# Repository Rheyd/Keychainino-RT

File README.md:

# Keychainino-RT
this is a fork of the original KeychaininoTHT https://github.com/alessandromatera/KeyChainino
this version allows you to make the Keychainino in a single layer PCB, with some wire bridges, but none the less allows you to make it, remember to support the original creator, Alessandromatera
Cheers.

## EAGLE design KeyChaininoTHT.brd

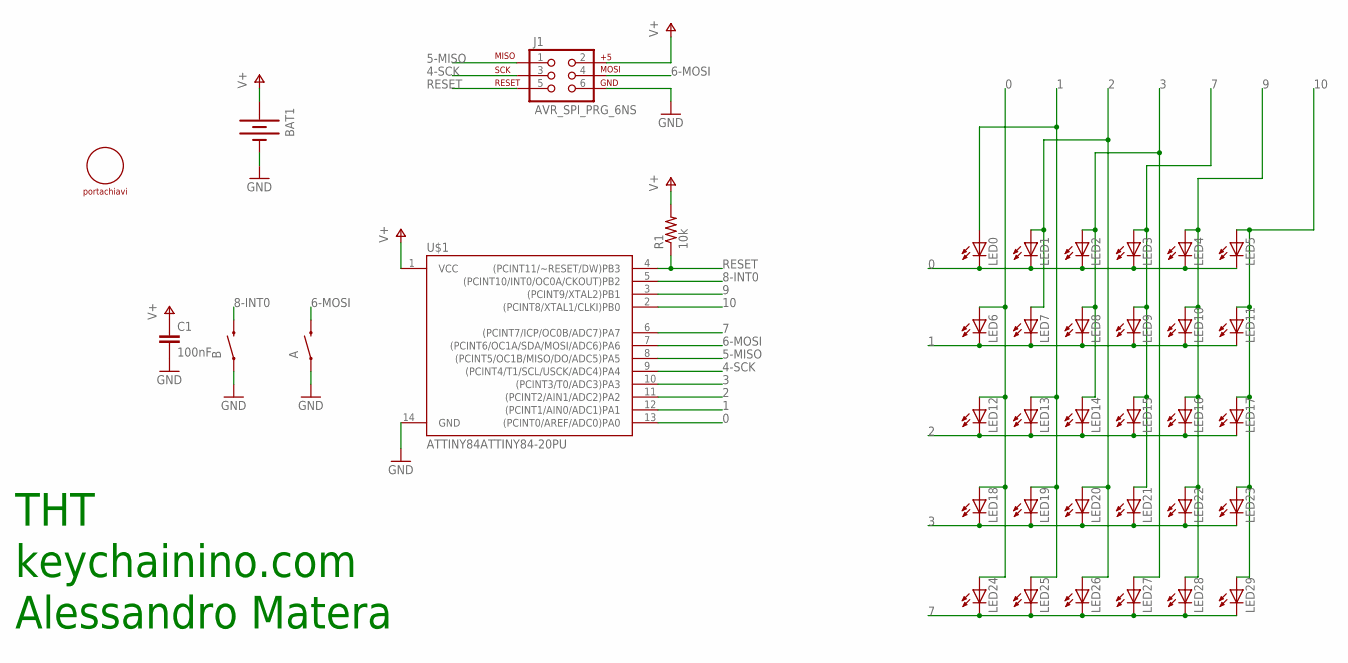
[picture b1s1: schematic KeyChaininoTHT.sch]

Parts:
A: SWITCH-MOMENTARY-2PTH; TACTILE-PTH
B: SWITCH-MOMENTARY-2PTH; TACTILE-PTH
BAT1: BATTERY20PTH; BATTCOM_20MM_PTH
C1: 100nF; CAP-PTH-5MM
J1: AVR_SPI_PRG_6NS; 2X3-NS
LED0, LED1, LED2, LED3, LED4, LED5, LED6, LED7, LED8, LED9, LED10, LED11, LED12, LED13, LED14, LED15, LED16, LED17, LED18, LED19, LED20, LED21, LED22, LED23, LED24, LED25, LED26, LED27, LED28, LED29: LED5MM-KIT
R1: 10k; R1206
U$1: ATTINY84ATTINY84-20PU; DIL14
U$2: ANELLO-PORTACHIAVI; HOLE-PORTACHIAVI

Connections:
0: LED0.K (C), LED1.K (C), LED2.K (C), LED3.K (C), LED4.K (C), LED5.K (C), LED6.A, LED12.A, LED18.A, LED24.A, U$1.13 ((PCINT0/AREF/ADC0)PA0)
1: LED0.A, LED6.K (C), LED7.K (C), LED8.K (C), LED9.K (C), LED10.K (C), LED11.K (C), LED13.A, LED19.A, LED25.A, U$1.12 ((PCINT1/AIN0/ADC1)PA1)
2: LED1.A, LED7.A, LED12.K (C), LED13.K (C), LED14.K (C), LED15.K (C), LED16.K (C), LED17.K (C), LED20.A, LED26.A, U$1.11 ((PCINT2/AIN1/ADC2)PA2)
3: LED2.A, LED8.A, LED14.A, LED18.K (C), LED19.K (C), LED20.K (C), LED21.K (C), LED22.K (C), LED23.K (C), LED27.A, U$1.10 ((PCINT3/T0/ADC3)PA3)
4-SCK: J1.3, U$1.9 ((PCINT4/T1/SCL/USCK/ADC4)PA4)
5-MISO: J1.1, U$1.8 ((PCINT5/OC1B/MISO/DO/ADC5)PA5)
6-MOSI: A.3 (2), J1.4, U$1.7 ((PCINT6/OC1A/SDA/MOSI/ADC6)PA6)
7: LED3.A, LED9.A, LED15.A, LED21.A, LED24.K (C), LED25.K (C), LED26.K (C), LED27.K (C), LED28.K (C), LED29.K (C), U$1.6 ((PCINT7/ICP/OC0B/ADC7)PA7)
8-INT0: B.3 (2), U$1.5 ((PCINT10/INT0/OC0A/CKOUT)PB2)
9: LED4.A, LED10.A, LED16.A, LED22.A, LED28.A, U$1.3 ((PCINT9/XTAL2)PB1)
10: LED5.A, LED11.A, LED17.A, LED23.A, LED29.A, U$1.2 ((PCINT8/XTAL1/CLKI)PB0)
GND: A.1, B.1, BAT1.2 (-), C1.2, J1.6, U$1.14 (GND)
RESET: J1.5, R1.1, U$1.4 ((PCINT11/~RESET/DW)PB3)
V+: BAT1.1 (+), C1.1, J1.2, R1.2, U$1.1 (VCC)

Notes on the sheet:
THT
keychainino.com
Alessandro Matera

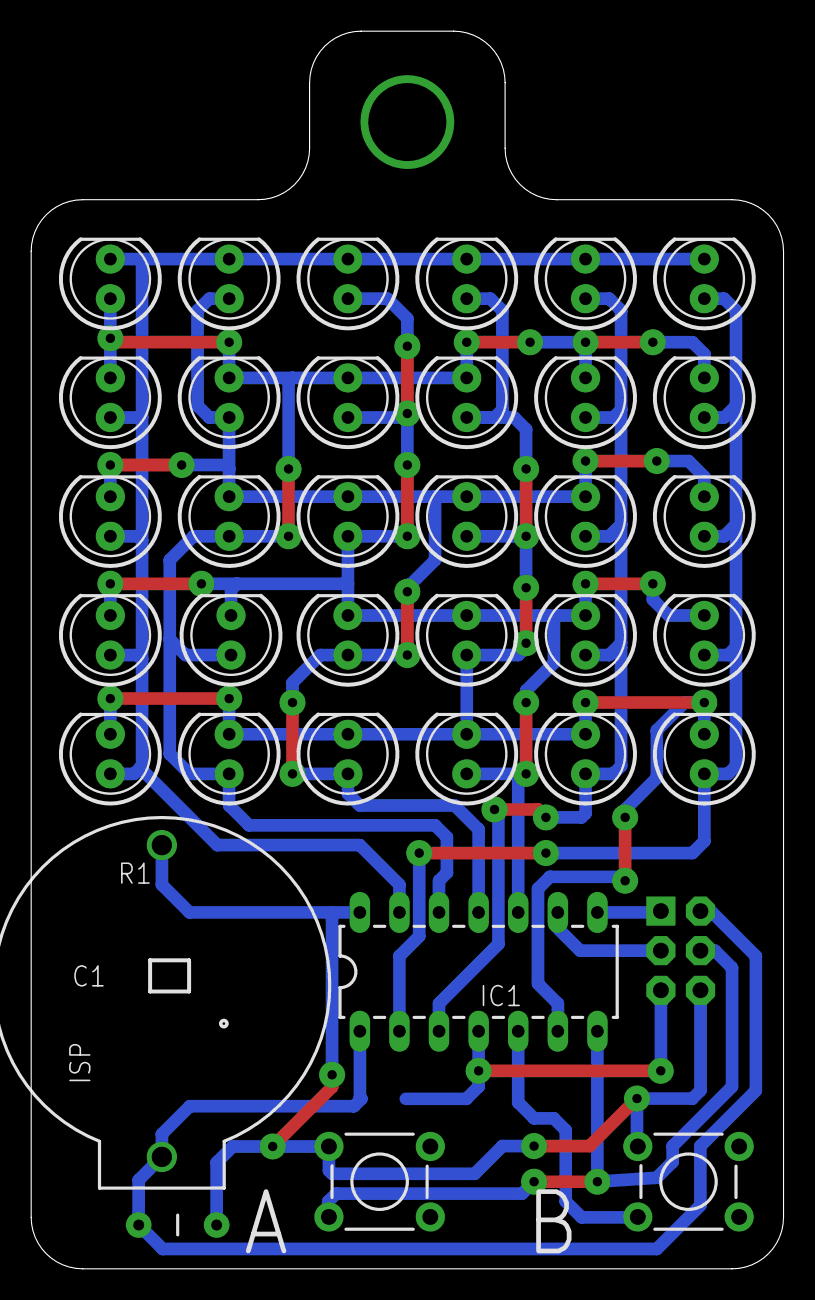
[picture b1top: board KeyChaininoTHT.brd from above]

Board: 2 copper layers, 48.3 x 79.4 mm, 38 parts (1 on the bottom side), 14 nets.

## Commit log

2018-07-16 Add files via upload
    This is the modified version of the Original Keychainino THT
    it was easier this way to make a single side PCB (with the help of some wire as bridges)

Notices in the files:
parts and their libraries:
SparkFun-Electromechanical: Licensing: CC v3.0 Share-Alike You are welcome to use this library for commercial purposes.
